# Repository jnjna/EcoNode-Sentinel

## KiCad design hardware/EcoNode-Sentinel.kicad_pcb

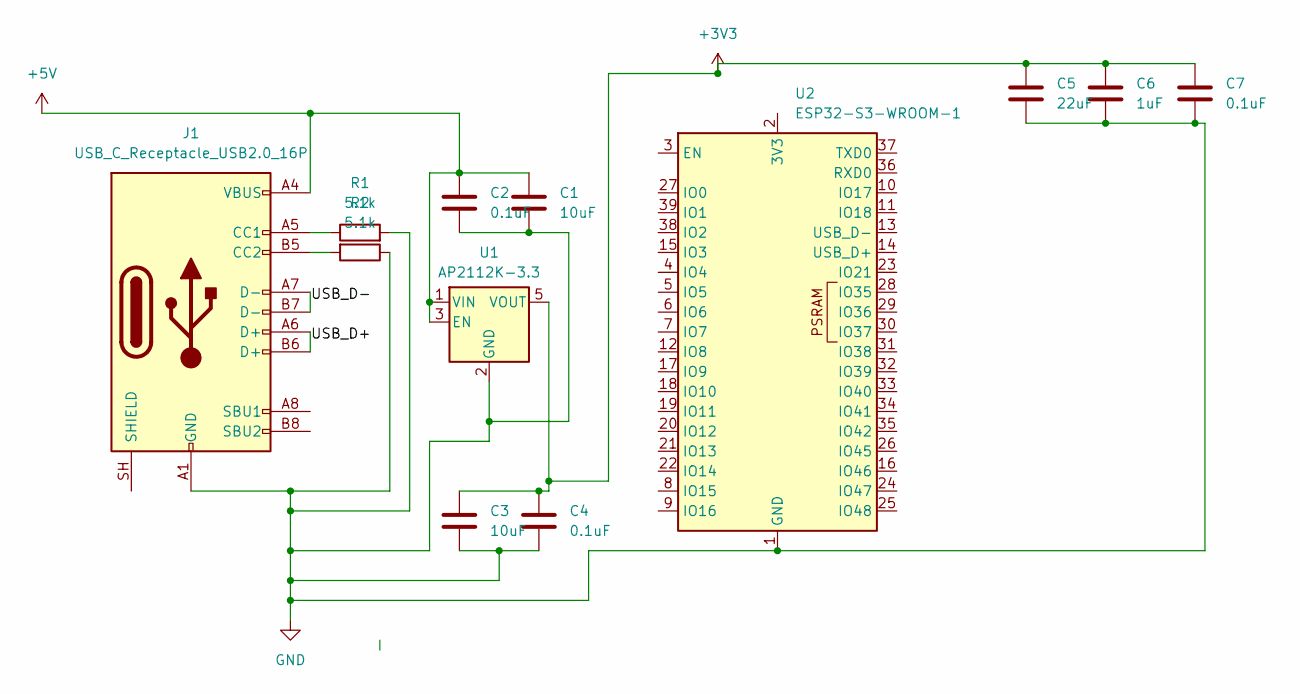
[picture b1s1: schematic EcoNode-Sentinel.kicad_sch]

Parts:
C1, C3: 10uF; C_0805_2012Metric
C2, C4, C7: 0.1uF; C_0603_1608Metric
C5: 22uF; C_1206_3216Metric
C6: 1uF; C_0603_1608Metric
J1: USB_C_Receptacle_USB2.0_16P; USB_C_Receptacle_GCT_USB4105-xx-A_16P_TopMnt_Horizontal
R1, R2: 5.1k; R_0603_1608Metric
U1: AP2112K-3.3; SOT-23-5
U2: ESP32-S3-WROOM-1

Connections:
+3V3: C3.1, C4.1, C5.1, C6.1, C7.1, U1.5 (VOUT)
+5V: C1.2, C2.1, J1.A4 (VBUS), J1.A9 (VBUS), J1.B4 (VBUS), J1.B9 (VBUS), U1.1 (VIN), U1.3 (EN)
/ USB_D+: J1.A6 (D+), J1.B6 (D+)
/USB_D-: J1.A7 (D-), J1.B7 (D-)
GND: C1.1, C2.2, C3.2, C4.2, C5.2, C6.2, C7.2, J1.A1 (GND), J1.A12 (GND), J1.B1 (GND), J1.B12 (GND), R1.2, R2.1, U1.2 (GND), U2.1 (GND), U2.40 (GND), U2.41 (GND)
unnamed: J1.A5 (CC1), R1.1
unnamed: J1.B5 (CC2), R2.2

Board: 4 copper layers, 12 parts (0 on the bottom side), 7 nets, no tracks yet.

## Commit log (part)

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2026-06-11 docs: initialize project PRD and hardware tradeoff matrix
2026-06-13 Design: Day 2 Complete - Initialized KiCad 10 project and 4-layer stackup
